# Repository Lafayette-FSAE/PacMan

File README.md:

# PacMan
A KiCad Schematic for PacMan, a Accumulator Management Board for the Lafayette FSAE Accumulator Management System

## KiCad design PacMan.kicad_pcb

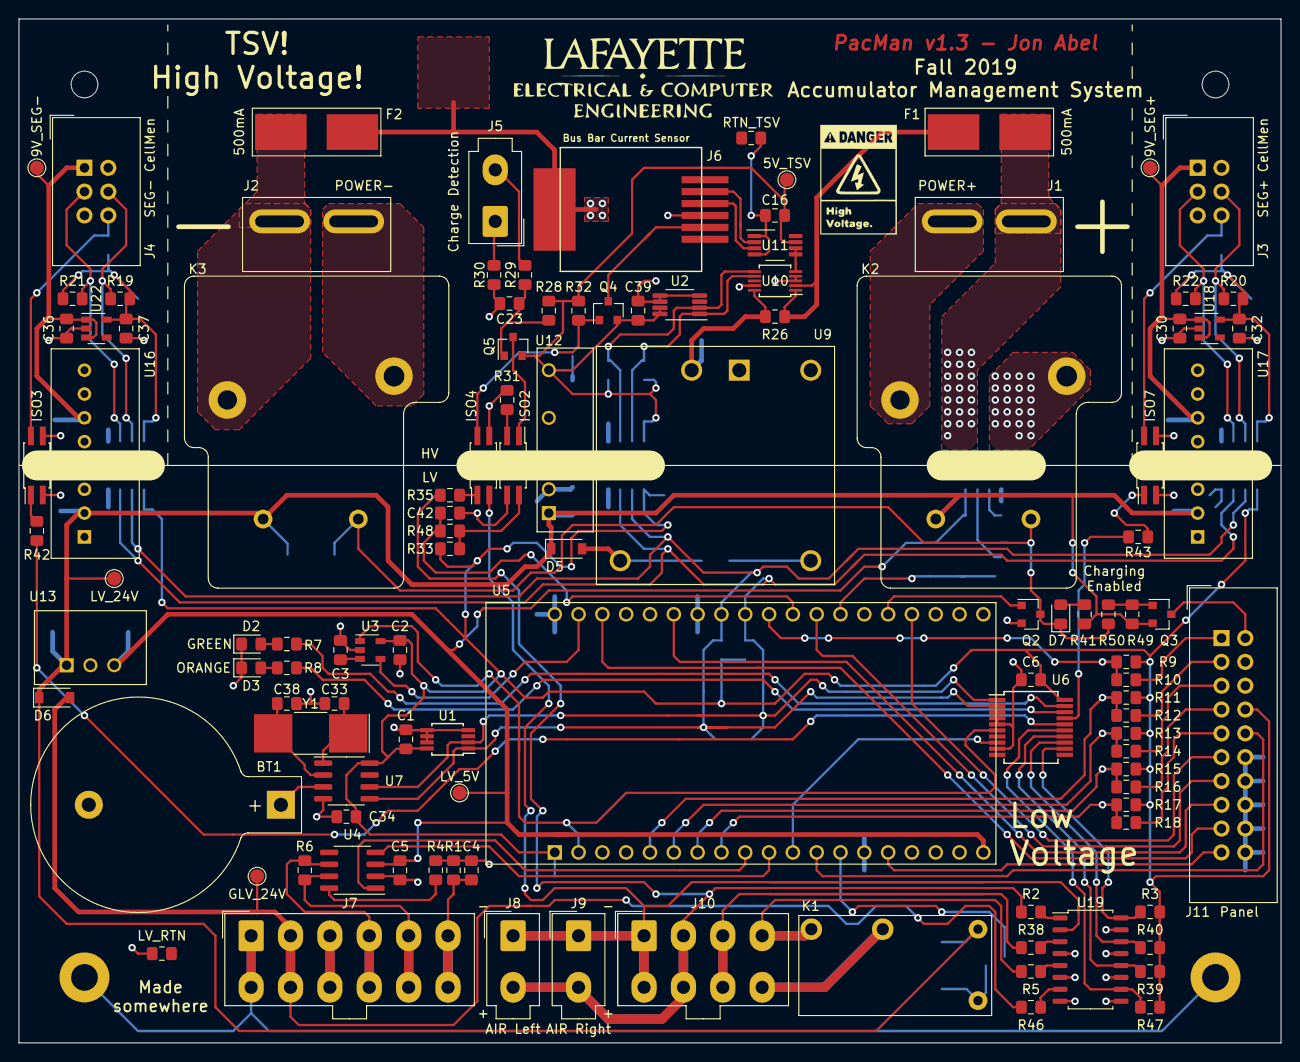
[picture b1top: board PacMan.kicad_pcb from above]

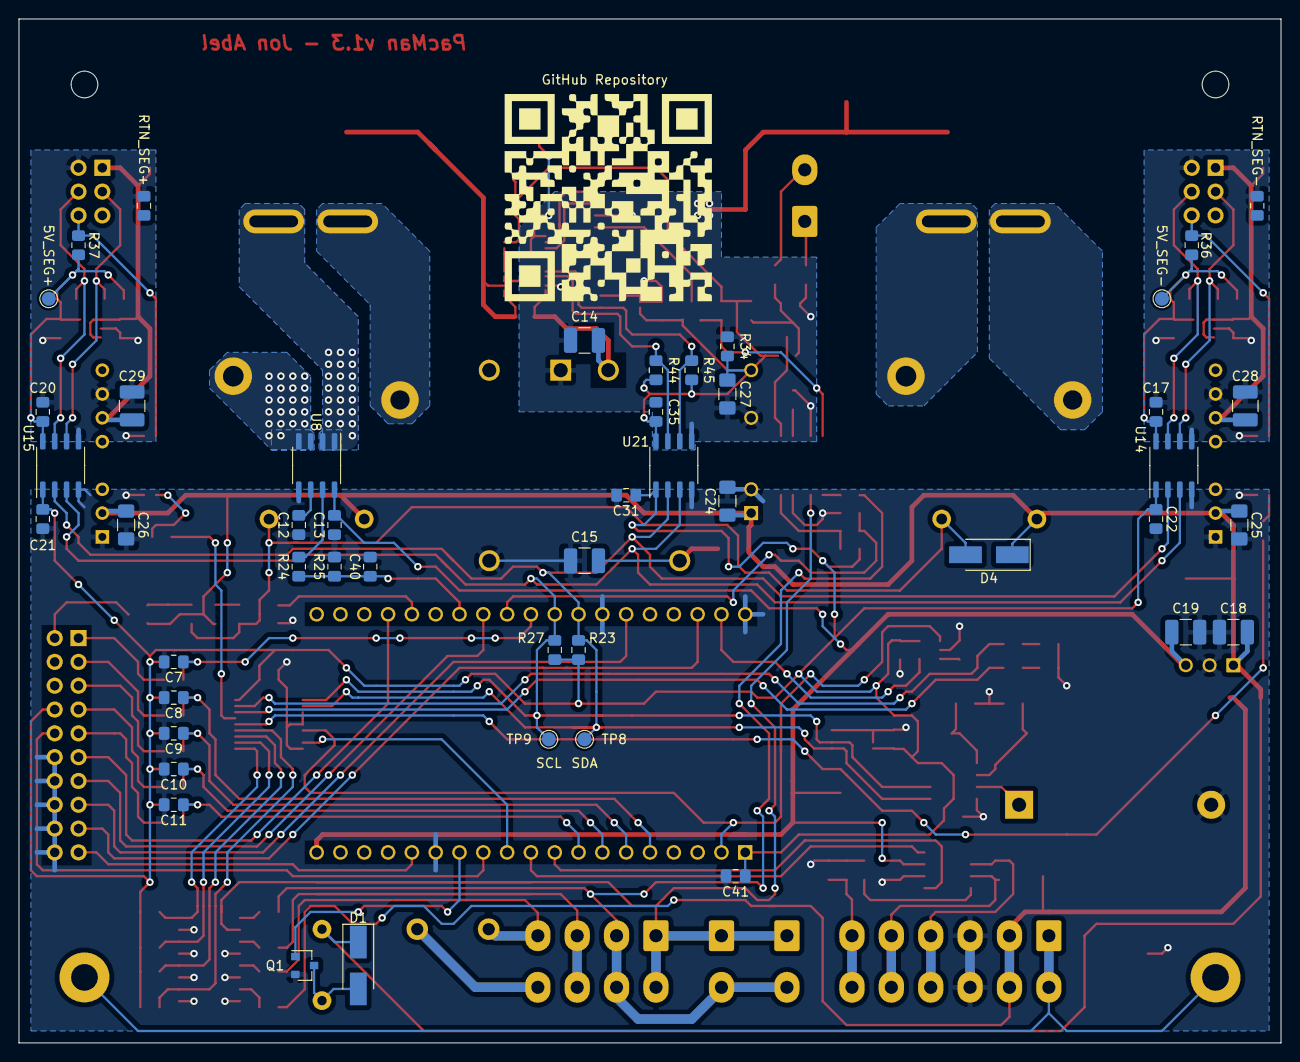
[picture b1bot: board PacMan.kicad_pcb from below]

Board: 2 copper layers, 134.6 x 109.2 mm, 168 parts (47 on the bottom side), 105 nets.

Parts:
BT1: BR1225; BatteryHolder_Keystone_103_1x20mm
C1, C2, C3, C5, C6, C7, C8, C9, C10, C11, C16, C17, C20, C21, C22, C23, C31, C35, C39: 0.1u/50V; C_0805_2012Metric_Pad1.15x1.40mm_HandSolder
C4, C42: C; C_0805_2012Metric_Pad1.15x1.40mm_HandSolder
C12: 1n/50V; C_0805_2012Metric_Pad1.15x1.40mm_HandSolder
C13, C30, C34, C36, C40, C41: 1u/50V; C_0805_2012Metric_Pad1.15x1.40mm_HandSolder
C14: 4.7u/100V; C_1210_3225Metric_Pad1.42x2.65mm_HandSolder
C15, C18, C28, C29: 10u/50V; C_1210_3225Metric_Pad1.42x2.65mm_HandSolder
C19: 22u/25V; C_1210_3225Metric_Pad1.42x2.65mm_HandSolder
C24, C25, C26, C27: 4.7uF/50V; C_1206_3216Metric_Pad1.42x1.75mm_HandSolder
C32, C37: 2.2u/25V; C_0805_2012Metric_Pad1.15x1.40mm_HandSolder
C33, C38: 20p; C_0805_2012Metric_Pad1.15x1.40mm_HandSolder
D1, D4: S1B; D_SMA_Handsoldering
D2: LED_GREEN; LED_0805_2012Metric_Pad1.15x1.40mm_HandSolder
D3: LED_ORANGE; LED_0805_2012Metric_Pad1.15x1.40mm_HandSolder
D5, D6: 1N5819HW; D_SOD-123
D7: LED_CHRG; LED_0805_2012Metric_Pad1.15x1.40mm_HandSolder
F1, F2: 500mA; 0154.500DRL
H1, H2: MountingHole_NoPad_#4; MountingHole_#4_NoPad
H3, H4: MountingHole_Pad_#4; MountingHole_#4_Pad
ISO2, ISO3, ISO4, ISO7: TLP293; SO-4_4.4x2.3mm_P1.27mm
J1: POWER+; Powerpole_PP45_FP_1x2
J2: POWER-; Powerpole_PP45_FP_1x2
J3: SEG+ CellMen; IDC-Header_2x03_P2.54mm_Vertical
J4: SEG- CellMen; IDC-Header_2x03_P2.54mm_Vertical
J5: Charge Detection; Molex_Mini-Fit_Jr_5566-02A_2x01_P4.20mm_Vertical
J6: BusBar Current Sensor; MOLEX_RJ11
J7: GLV/CAN; Molex_Mini-Fit_Jr_5566-12A_2x06_P4.20mm_Vertical
J8: AIR Left; Molex_Mini-Fit_Jr_5566-02A_2x01_P4.20mm_Vertical
J9: AIR Right; Molex_Mini-Fit_Jr_5566-02A_2x01_P4.20mm_Vertical
J10: SLOOP; Molex_Mini-Fit_Jr_5566-08A_2x04_P4.20mm_Vertical
J11: Panel; Amphenol_IDC-Header_2x10_P2.54mm_Vertical
K1: G5Q-1A4 DC24; G5Q-1A4
K2, K3: T9AS1D12-24; T9AS1D12
LOGO1: LafECEDepLogo; ECE_Logo_Jon
LOGO2: LeopardPawLogo; paw_solder_mask_bigly
LOGO3: DangerHighVoltageLogo; highvoltagesmall
Q1, Q2: DMN3730U; SOT-23
Q3, Q4, Q5: DMP10H4D2S; SOT-23
R1: 1M; R_0805_2012Metric_Pad1.15x1.40mm_HandSolder
R2, R5, R35, R38, R46: 5.1k; R_0805_2012Metric_Pad1.15x1.40mm_HandSolder
R3, R24, R32, R33, R36, R37, R39, R40, R47: 10k; R_0805_2012Metric_Pad1.15x1.40mm_HandSolder
R4, R10, R12, R14, R16, R18, R41: 1k; R_0805_2012Metric_Pad1.15x1.40mm_HandSolder
R6: 120; R_0805_2012Metric_Pad1.15x1.40mm_HandSolder
R7, R8, R42, R43: 270; R_0805_2012Metric_Pad1.15x1.40mm_HandSolder
R9, R11, R13, R15, R17, R28: 100k; R_0805_2012Metric_Pad1.15x1.40mm_HandSolder
R19, R20, R21, R22, R23, R27, R44, R45: 3.3k; R_0805_2012Metric_Pad1.15x1.40mm_HandSolder
R25: 22k; R_0805_2012Metric_Pad1.15x1.40mm_HandSolder
R26: 0.82; R_0805_2012Metric_Pad1.15x1.40mm_HandSolder
R29, R30: 5k; R_0805_2012Metric_Pad1.15x1.40mm_HandSolder
R31: 330; R_0805_2012Metric_Pad1.15x1.40mm_HandSolder
R34: 470; R_0805_2012Metric_Pad1.15x1.40mm_HandSolder
R48: R; R_0805_2012Metric_Pad1.15x1.40mm_HandSolder
R49, R50: 4.7k; R_0805_2012Metric_Pad1.15x1.40mm_HandSolder
TP1: 5V_SEG-; TestPoint_Pad_D1.5mm
TP2: RTN_SEG-; R_0805_2012Metric_Pad1.15x1.40mm_HandSolder
TP3: 9V_SEG-; TestPoint_Pad_D1.5mm
TP4: LV_RTN; R_0805_2012Metric_Pad1.15x1.40mm_HandSolder
TP5: LV_5V; TestPoint_Pad_D1.5mm
TP6: LV_24V; TestPoint_Pad_D1.5mm
TP7: GLV_24V; TestPoint_Pad_D1.5mm
TP8: SDA; TestPoint_Pad_D1.5mm
TP9: SCL; TestPoint_Pad_D1.5mm
TP10: 5V_TSV; TestPoint_Pad_D1.5mm
TP11: RTN_TSV; R_0805_2012Metric_Pad1.15x1.40mm_HandSolder
TP12: 9V_SEG+; TestPoint_Pad_D1.5mm
TP13: 5V_SEG+; TestPoint_Pad_D1.5mm
TP14: RTN_SEG+; R_0805_2012Metric_Pad1.15x1.40mm_HandSolder
U1, U2: MCP9804; MSOP-8_3x3mm_P0.65mm
U3: ADM6320; SOT-23-5
U4: MCP2551-I-SN; SOIC-8_3.9x4.9mm_P1.27mm
U5: ESP32_DEVKITC; MODULE_ESP32-DEVKITC-32D
U6: MCP23008; SSOP-20_5.3x7.2mm_P0.65mm
U7: BQ32002; SOIC-8_3.9x4.9mm_P1.27mm
U8: ACHS-7122; SO-8_3.9x4.9mm_P1.27mm
U9: PDQE10-Q48-S24-D; PDQE10-DIP6
U10: LTC4151; MSOP-10_3x3mm_P0.5mm
U11: INA592; VSSOP-8_3.0x3.0mm_P0.65mm
U12: MEF1S2405SP3C
U13: V7805-500; VX7805-500
U14, U15, U21: Si8600AC; SO-8_3.9x4.9mm_P1.27mm
U16, U17: TEC3-2419
U18, U22: AP2204K-5.0; SOT-23-5
U19: TLP293-4; SOIC-16_4.55x10.3mm_P1.27mm
Y1: 32K; Crystal_SMD_SeikoEpson_MC405-2Pin_9.6x4.1mm

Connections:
/5V_SEG+: C20.1, C32.1, R20.1, R22.1, R37.1, TP13.1, U15.8, U18.5
/5V_SEG-: C17.1, C37.1, R19.1, R21.1, R36.1, TP1.1, U14.8, U22.5
/5V_TSV: C16.2, C27.1, C35.1, C39.1, Q4.2, Q5.2, R28.1, R32.1, R34.1, R44.1, R45.1, TP10.1, U2.7, U2.8, U11.7, U12.7, U21.8
/9V_SEG+: C29.1, C30.1, J3.1, TP12.1, U17.6, U18.1, U18.3
/9V_SEG-: C28.1, C36.1, J4.1, TP3.1, U16.6, U22.1, U22.3
/AIRS+: J8.2, J9.2, J10.2, J10.6, R2.2, R35.2
/AIRS-: ISO4.2, J8.1, J9.1, J10.1, J10.5, U19.2
/AMPS_PWR: J6.5, Q4.3
/BTN_CENTER: J11.9, R18.1
/BTN_DOWN: J11.7, R16.1
/BTN_LEFT: J11.1, R10.1
/BTN_RIGHT: J11.3, R12.1
/BTN_UP: J11.5, R14.1
/CAN_H: J7.5, J7.11, R6.1, U4.7
/CAN_L: J7.4, J7.10, R6.2, U4.6
/CAN_SHIELD: C4.2, J7.6, J7.12, R1.2
/CHRG_CURRENT: C40.1, R24.1, R25.1, U5.32
/CHRG_DETECT+: J5.2, R29.2
/CHRG_DETECT-: J5.1, R30.2
/CHRG_EN: Q2.1, U5.34
/CHRG_IN+: J1.2, K2.3
/CHRG_IN-: J2.1, K3.4
/CHRG_LED: J11.2, Q3.3
/CHS_GND: H3.1, H4.1, J7.1, J7.7
/Charging/CurrentSensor+: K2.4, U8.3, U8.4
/DCHRG_A1: J6.3, U11.3
/DCHRG_A2: J6.2, U11.2
/DISP_BUSY: J11.13, U5.31
/DISP_CLK: J11.10, U5.12
/DISP_CS: J11.11, U5.35
/DISP_DC: J11.17, U5.22
/DISP_DIN: J11.19, U5.15
/DISP_RST: J11.15, U5.25
/GLV_24V: D6.2, J7.2, J7.8, R46.2, TP7.1
/GLV_RTN: BT1.2, C1.2, C2.2, C3.2, C4.1, C5.2, C6.2, C7.2, C8.2, C9.2, C10.2, C11.2, C12.2, C13.2, C15.2, C18.2, C19.2, C21.2, C22.2, C24.2, C25.2, C26.2, C31.2, C33.2, C34.2, C38.2, C40.2, C41.2, C42.2, D2.1, D3.1, ISO2.3, ISO3.2, ISO7.2, J7.3, J7.9, J11.12, J11.14, J11.16, J11.18, J11.20, Q1.2, Q2.2, R1.1, R4.1, R25.2, TP4.1, U1.4, U1.5, U1.6, U1.7, U3.2, U4.2, U5.14, U5.20, U5.26, U6.3, U6.4, U6.5, U6.9, U7.4, U8.5, U9.5, U12.2, U13.2, U14.4, U15.4, U16.1, U17.1, U19.4, U19.6, U19.8, U19.9, U19.11, U19.13, U19.15, U21.4
/Isolation/EN_AMPS: ISO4.4, Q4.1, R32.2
/LV_3V3: C1.1, C2.1, C6.1, C21.1, C22.1, C31.1, C34.1, C41.1, J11.8, R3.2, R9.1, R11.1, R13.1, R15.1, R17.1, R23.1, R27.1, R33.2, R39.2, R40.2, R47.2, U1.8, U3.5, U5.1, U6.20, U7.8, U14.1, U15.1, U21.1
/LV_5V: C5.1, C13.1, C19.1, TP5.1, U4.3, U5.19, U8.8, U13.3
/LV_24V: C18.1, C24.1, C25.1, C26.1, D1.1, D4.1, D5.1, D6.1, K1.1, K2.1, K3.1, Q3.2, R41.1, R49.1, TP6.1, U12.1, U13.1, U16.2, U17.2
/MCU/AIRS_STATUS: R3.1, U6.12, U19.16
/MCU/BTN_CENTER_MCU: C11.1, R17.2, R18.2, U5.8
/MCU/BTN_DOWN_MCU: C10.1, R15.2, R16.2, U5.7
/MCU/BTN_LEFT_MCU: C7.1, R9.2, R10.2, U5.29
/MCU/BTN_RIGHT_MCU: C8.1, R11.2, R12.2, U5.5
/MCU/BTN_UP_MCU: C9.1, R13.2, R14.2, U5.6
/MCU/CANRX: U4.4, U5.10
/MCU/CANTX: U4.1, U5.9
/MCU/GLV_STATUS: R47.1, U6.15, U19.10
/MCU/IO_INT: U5.11, U6.8
/MCU/LED_G: R7.1, U6.19
/MCU/LED_O: R8.1, U6.18
/MCU/SLOOP1_STATUS: R39.1, U6.14, U19.12
/MCU/SLOOP2_STATUS: R40.1, U6.13, U19.14
/MCU/SLOOP_EN: Q1.1, U5.13
/MCU/WATCHDOG: U3.4, U5.21
/MCU/~RESET: U3.1, U5.2, U6.6
/PACK+: F1.1, J1.1, U8.1, U8.2
/PACK-: F2.1, J2.2, K3.3
/PACK_FUSED: F1.2, R26.2, U10.1, U10.2
/PACK_RTN: C14.2, C16.1, C23.2, C27.2, C35.2, C39.2, F2.2, ISO4.3, J6.4, J6.SH, R30.1, R31.1, R34.2, TP11.1, U2.4, U2.5, U2.6, U9.1, U10.3, U10.4, U10.9, U11.1, U11.4, U12.5, U21.5
/Power/DCHRG_CURRENT: U10.5, U11.5, U11.6
/Power/PACK_FUSED_CS: C14.1, R26.1, U9.2, U10.10
/RST_GLV_SEG+: R43.2, U6.17
/RST_GLV_SEG-: R42.2, U6.16
/RST_SEG+: ISO7.4, J3.6, R37.2
/RST_SEG-: ISO3.4, J4.6, R36.2
/RTN_SEG+: C20.2, C29.2, C30.2, C32.2, ISO7.3, J3.2, TP14.1, U15.5, U17.7, U18.2
/RTN_SEG-: C17.2, C28.2, C36.2, C37.2, ISO3.3, J4.2, TP2.1, U14.5, U16.7, U22.2
/SCL_GLV: R27.2, TP9.1, U1.2, U5.28, U6.1, U7.6, U14.3, U15.3, U21.3
/SCL_SEG+: J3.3, R22.2, U15.6
/SCL_SEG-: J4.3, R21.2, U14.6
/SCL_TSV: R45.2, U2.2, U10.6, U21.6
/SDA_GLV: R23.2, TP8.1, U1.1, U5.27, U6.2, U7.5, U14.2, U15.2, U21.2
/SDA_SEG+: J3.4, R20.2, U15.7
/SDA_SEG-: J4.4, R19.2, U14.7
/SDA_TSV: R44.2, U2.1, U10.7, U21.7
/SLOOP1_IN: J10.4, K1.4, R5.2
/SLOOP1_OUT: J10.8, K1.3
/SLOOP2: J10.3, J10.7, R38.2
/~CHRG_DETECT: C42.1, R48.1, U5.30
unnamed: BT1.1, U7.3
unnamed: C3.1, U3.3
unnamed: C12.1, U8.6
unnamed: C15.1, D5.2, U9.3
unnamed: C23.1, Q5.1, R28.2, R29.1
unnamed: C33.1, U7.1, Y1.1
unnamed: C38.1, U7.2, Y1.2
unnamed: D1.2, K1.2, Q1.3
unnamed: D2.2, R7.2
unnamed: D3.2, R8.2
unnamed: D4.2, D7.1, K2.2, K3.2, Q2.3, R50.2
unnamed: D7.2, R41.2
unnamed: ISO2.1, Q5.3
unnamed: ISO2.2, R31.2
unnamed: ISO2.4, R33.1, R48.2
unnamed: ISO3.1, R42.1
unnamed: ISO4.1, R35.1
unnamed: ISO7.1, R43.1
unnamed: Q3.1, R49.2, R50.1
unnamed: R2.1, U19.1
unnamed: R4.2, U4.8
unnamed: R5.1, U19.5
unnamed: R24.2, U8.7
unnamed: R38.1, U19.3
unnamed: R46.1, U19.7

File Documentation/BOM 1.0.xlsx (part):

C4 | C | Capacitor_SMD:C_0805_2012Metric_Pad1.15x1.40mm_HandSolder | ~ |  |  |  |  | 1
> C1-C3, C5-C11, C16, C22-C25 | 0.1u/50V | Capacitor_SMD:C_0805_2012Metric_Pad1.15x1.40mm_HandSolder | http://www.samsungsem.com/kr/support/product-search/mlcc/__i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 | Samsung Electro-Mechanics | CL21B104KBCNNNC | Digikey | 1276-1003-1-ND | 15
C12 | 1n/50V | Capacitor_SMD:C_0805_2012Metric_Pad1.15x1.40mm_HandSolder | http://www.samsungsem.com/kr/support/product-search/mlcc/__i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 | Samsung Electro-Mechanics | CL21B102KBCNNNC | Digikey | 1276-2425-1-ND | 1
C13 | 1u/50V | Capacitor_SMD:C_0805_2012Metric_Pad1.15x1.40mm_HandSolder | http://www.samsungsem.com/kr/support/product-search/mlcc/__i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 | Samsung Electro-Mechanics | CL21B105KBFNNNG | Digikey | 1276-6470-1-ND | 1
C14 | 4.7u/100V | Capacitor_SMD:C_0805_2012Metric_Pad1.15x1.40mm_HandSolder | http://www.samsungsem.com/kr/support/library/product-catalog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 | Samsung Electro-Mechanics | CL32B475KCVZW6E | Digikey | 1276-7060-1-ND | 1
> C15, C18, C20 | 10u/50V | Capacitor_SMD:C_1210_3225Metric_Pad1.42x2.65mm_HandSolder | http://www.samsungsem.com/kr/support/product-search/mlcc/__i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 | Samsung Electro-Mechanics | CL32B106KBJNNWE | Digikey | 1276-3388-1-ND | 3
C17 | 22u/50V | Capacitor_SMD:C_0805_2012Metric_Pad1.15x1.40mm_HandSolder | http://www.samsungsem.com/kr/support/product-search/mlcc/__i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 | Samsung Electro-Mechanics | CL21A475KBQNNNE | Digikey | 1276-1248-1-ND | 1
C19 | 22u/25V | Capacitor_SMD:C_1210_3225Metric_Pad1.42x2.65mm_HandSolder | http://www.samsungsem.com/kr/support/product-search/mlcc/__i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 | Samsung Electro-Mechanics | CL32B226KAJNFNE | Digikey | 1276-3391-1-ND | 1
C21 | 0.33u/50V | Capacitor_SMD:C_0805_2012Metric_Pad1.15x1.40mm_HandSolder | http://www.samsungsem.com/kr/support/product-search/mlcc/__i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 | Samsung Electro-Mechanics | CL21B334KBFNNNE | Digikey | 1276-1123-1-ND | 1
> D1, D4 | S1B | Diode_SMD:D_SMA_Handsoldering | https://www.diodes.com/assets/Datasheets/ds16003.pdf | Diodes Incorporated | S1B-13-F | Digikey | S1B-FDICT-ND | 2
D2 | LED_GREEN | LED_SMD:LED_0805_2012Metric_Pad1.15x1.40mm_HandSolder | https://media.digikey.com/pdf/Data%20Sheets/Lite-On%20PDFs/L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 | Lite-On Inc. | LTST-C170GKT | Digikey | 160-1179-1-ND | 1
D3 | LED_ORANGE | LED_SMD:LED_0805_2012Metric_Pad1.15x1.40mm_HandSolder | http://optoelectronics.liteon.com/upload/download/DS-22-99-0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 | Lite-On Inc. | LTST-C171AKT | Digikey | 160-1419-1-ND | 1
> D5, D6 | 1N5819HW | Diode_SMD:D_SOD-123 | https://www.diodes.com/assets/Datasheets/ds30217.pdf | Diodes Incorporated | 1N5819HW-7-F | Digikey | 1N5819HW-FDICT-ND | 2
F1 | Pack+ | Lafayette_Electric_Car_Footprints:0154.500DRL | https://www.littelfuse.com/~/media/electronics/datasheets/fu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 | Littelfuse Inc. | 0154.500DRL | Digikey | F6776CT-ND | 1
F2 | Pack- | Lafayette_Electric_Car_Footprints:0154.500DRL | https://www.littelfuse.com/~/media/electronics/datasheets/fu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 | Littelfuse Inc. | 0154.500DRL | Digikey | F6776CT-ND | 1
> H1-H4 | MountingHole_Pad | MountingHole:MountingHole_4.3mm_M4_Pad | ~ |  |  |  |  | 4
> ISO1-ISO4 | TLP293 | Package_SO:SO-4_4.4x2.3mm_P1.27mm | https://toshiba.semicon-storage.com/info/docget.jsp?did=1441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 | Toshiba Semiconductor | TLP293(GR-TPL,E | Digikey | TLP293(GR-TPLECT-ND | 4
J1 | POWER+ | Lafayette_Electric_Car_Footprints:DF22-2P-7.92 | https://www.hirose.com/product/document?clcode=CL0680-1074-0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 | Hirose Electric Co | DF22L-2P-7.92DSA(05) | Digikey | H10722-ND | 1
J2 | POWER- | Lafayette_Electric_Car_Footprints:DF22-2P-7.92 | https://www.hirose.com/product/document?clcode=CL0680-1074-0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 | Hirose Electric Co | DF22R-2P-7.92DSA(05) | Digikey | H10718-ND | 1
J3 | TSV IN | Lafayette_Electric_Car_Footprints:Molex_Mini-Fit_Jr_5566-02A_2x01_P4.20mm_Verti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 | https://www.molex.com/webdocs/datasheets/pdf/en-us/172447020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 | Molex | 1724470202 | Digikey | WM17931-ND | 1
J4 | Charge Detection | Lafayette_Electric_Car_Footprints:Molex_Mini-Fit_Jr_5566-02A_2x01_P4.20mm_Verti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 | https://www.molex.com/webdocs/datasheets/pdf/en-us/172447020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 | Molex | 1724470202 | Digikey | WM17931-ND | 1
J5 | CellMen | Connector_IDC:IDC-Header_2x03_P2.54mm_Vertical | https://cdn.amphenol-icc.com/media/wysiwyg/files/drawing/75869.pdf | Amphenol ICC | 75869-131LF | Digikey | 609-2845-ND | 1
J6 | RJ12 | Lafayette_Electric_Car_Footprints:MOLEX_RJ11 | https://www.molex.com/pdm_docs/sd/855135002_sd.pdf | Molex | 855135002 | Digikey | WM3789CT-ND | 1
J7 | Panel | Lafayette_Electric_Car_Footprints:Amphenol_IDC-Header_2x10_P2.54mm_Vertical | https://cdn.amphenol-icc.com/media/wysiwyg/files/drawing/75869.pdf | Amphenol ICC | 75869-304LF | Digikey | 609-5118-ND | 1
J8 | SLOOP | Lafayette_Electric_Car_Footprints:Molex_Mini-Fit_Jr_5566-08A2_2x04_P4.20mm_Vert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 | https://www.molex.com/pdm_docs/sd/1724470002_sd.pdf | Molex | 1724470008 | Digikey | WM20746-ND | 1
J9 | GLV/CAN | Lafayette_Electric_Car_Footprints:Molex_Mini-Fit_Jr_5566-12A2_2x06_P4.20mm_Vert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 | https://www.molex.com/pdm_docs/sd/462070012_sd.pdf | Molex | 462070012 | Digikey | 23-0462070012-ND | 1
J12 | CHRG TEST | Connector_PinHeader_2.54mm:PinHeader_1x02_P2.54mm_Vertical | ~ |  |  |  |  | 1
J13 | AIR Left | Lafayette_Electric_Car_Footprints:Molex_Mini-Fit_Jr_5566-02A_2x01_P4.20mm_Verti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 | https://www.molex.com/webdocs/datasheets/pdf/en-us/172447020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 | Molex | 1724470202 | Digikey | WM17931-ND | 1
J14 | AIR Right | Lafayette_Electric_Car_Footprints:Molex_Mini-Fit_Jr_5566-02A_2x01_P4.20mm_Verti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 | https://www.molex.com/webdocs/datasheets/pdf/en-us/172447020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 | Molex | 1724470202 | Digikey | WM17931-ND | 1
K1 | G5Q-1A4 DC24 | Lafayette_Electric_Car_Footprints:G5Q-1A4 | https://omronfs.omron.com/en_US/ecb/products/pdf/en-g5q.pdf | Omron Electronics | G5Q-1A4 DC24 | Digikey | Z224-ND | 1
> K2, K3 | T9AS1D12-48 | Lafayette_Electric_Car_Footprints:T9AS1D12 | https://www.te.com/commerce/DocumentDelivery/DDEController?A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 | TE Connectivity | T9AS1D12-48 | Digikey | PB1013-ND | 2
LOGO1 | LafECEDepLogo | Lafayette_Electric_Car_Footprints:ECE_Logo_Jon |  |  |  |  |  | 1
LOGO2 | LeopardPawLogo | Lafayette_Electric_Car_Footprints:paw_solder_mask_larger |  |  |  |  |  | 1
LOGO3 | DangerHighVoltageLogo | Lafayette_Electric_Car_Footprints:highvoltagesmall |  |  |  |  |  | 1
> Q1, Q3 | BSS123 | Package_TO_SOT_SMD:SOT-23_Handsoldering | https://www.diodes.com/assets/Datasheets/ds30366.pdf | Diodes Incorporated | BSS123-7-F | Digikey | BSS123-FDICT-ND | 2
> Q2, Q4 | DMP10H4D2S | Package_TO_SOT_SMD:SOT-23_Handsoldering | https://www.diodes.com/assets/Datasheets/DMP10H4D2S.pdf | Diodes Incorporated | DMP10H4D2S-7 | Digikey | DMP10H4D2S-7DICT-ND | 2
R1 | 1M | Resistor_SMD:R_0805_2012Metric_Pad1.15x1.40mm_HandSolder | ~ |  |  |  |  | 1
> R2, R28, R33-R37 | 4.7k | Resistor_SMD:R_0805_2012Metric_Pad1.15x1.40mm_HandSolder | ~ |  |  |  |  | 7
> R3, R24, R32 | 10k | Resistor_SMD:R_0805_2012Metric_Pad1.15x1.40mm_HandSolder | ~ |  |  |  |  | 3
> R4, R10, R12, R14, R16, R18, R22 | 1k | Resistor_SMD:R_0805_2012Metric_Pad1.15x1.40mm_HandSolder | ~ |  |  |  |  | 7
R6 | 120 | Resistor_SMD:R_0805_2012Metric_Pad1.15x1.40mm_HandSolder | ~ |  |  |  |  | 1
> R7, R8 | 270 | Resistor_SMD:R_0805_2012Metric_Pad1.15x1.40mm_HandSolder | ~ |  |  |  |  | 2
> R9, R11, R13, R15, R17 | 100k | Resistor_SMD:R_0805_2012Metric_Pad1.15x1.40mm_HandSolder | ~ |  |  |  |  | 5
R19 | 15k | Resistor_SMD:R_0805_2012Metric_Pad1.15x1.40mm_HandSolder | ~ |  |  |  |  | 1
> R20, R21 | 560 | Resistor_SMD:R_0805_2012Metric_Pad1.15x1.40mm_HandSolder | ~ |  |  |  |  | 2
R23 | 390 | Resistor_SMD:R_0805_2012Metric_Pad1.15x1.40mm_HandSolder | ~ |  |  |  |  | 1
R25 | 22k | Resistor_SMD:R_0805_2012Metric_Pad1.15x1.40mm_HandSolder | ~ |  |  |  |  | 1
R26 | 0.82 | Resistor_SMD:R_0805_2012Metric_Pad1.15x1.40mm_HandSolder | https://industrial.panasonic.com/cdbs/www-data/pdf/RDN0000/A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 | Panasonic Electronic Components | ERJ-6DQFR82V | Digikey | P19306CT-ND | 1
R27 | R | Resistor_SMD:R_0805_2012Metric_Pad1.15x1.40mm_HandSolder | ~ |  |  |  |  | 1
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
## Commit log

2019-10-08 Created blank schematic
2019-11-08 lotsa work
2019-11-08 more files
2019-11-10 v0.1, basic components on schematic
2019-11-11 Additional components and connectors, resistor sizing, etc.
2019-11-11 New power monitor, panel outputs and filtering, shunt resistor
2019-11-12 Routed almost everything, general design mostly complete
2019-11-13 Spec'd some parts
2019-11-13 Weird cache stuff
2019-11-13 More part speccing
2019-11-13 updated footprints
2019-11-14 Started work on board layout
2019-11-15 go on, look, see if I care
2019-11-15 routing
2019-11-18 added like 2 traces
2019-11-18 Changed/added some footprints for AIR and ChrgDetect connectors
2019-11-18 Routing + 3D models
2019-11-18 guess
2019-11-18 5ish more traces left wawaweewa
2019-11-19 filled out some parts information
2019-11-19 0 unrouted babyyyyyyyyy
2019-11-19 Gerber files from first review/quote
2019-11-19 GTD file
2019-11-19 Ordered board, GTD file, panelized gerbers
2019-11-19 v1.0
2019-11-20 Created schematic pdf for 1.0
2019-11-22 Added things to fix text file
2019-12-04 Updated Things to fix and added a render file
2019-12-07 Added BOM, some PDFs, updated schematic version to 1.1 for updates
2019-12-09 Updated things to fix, output some new renders, updated schematic to 1.1 to start changing
2020-01-04 Switched some pins around, added SLOOP isolators to measure SLOOP1in and SLOOP2
2020-01-04 brought in the updated fuse footprint and cleaned up some tracks
2020-01-04 removed fp-info-cache from git tracking
2020-01-06 made the board smaller
2020-01-07 starting the rework to fix the AMS isolation error
2020-01-07 Updated date for version on PCB
2020-01-08 Switched the control loops for the charging relays to GLV
2020-01-10 Updated some power stuff
2020-01-11 Started work on new layout
2020-01-11 quick change
2020-01-12 Added connectors for cell balancing, made big progress on new layout
2020-01-13 Just about finished the layout
2020-01-13 Started adding active charge measurement
2020-01-14 Added RTC onto board
2020-01-14 Schematic work, placed some components on the PCB
2020-01-14 started moving over to new esp dev kit
2020-01-15 Re-layout to account for the new esp32, put on the RTC, the balancing measurement stuff, pretty much finished up the board, added some comments to schematic and other changes
2020-01-15 switched some ESP32 pins around, hopefully fixed some grounding stuff, cleaned up schematic naming slightly
2020-01-17 Added connection to IO expander interrupt pin
2020-01-17 Added some planes around the balancing connectors and added the QRCode to the github page
2020-01-19 started re-routing for adjusted symmetric design
2020-01-20 incremental work
2020-01-20 Fixed a little bit of stuff
2020-01-21 completed reroute
2020-01-21 updayed relayfootprint and fixed chassis trace
2020-01-21 Cleaned up some spacing, silkscreen, qrcode
2020-01-21 Added CellMen reset lines and routed them
2020-01-22 quick track fix
2020-01-22 Output some gerber files and pushed some title block info
2020-01-22 Added panelized production files
2020-01-22 changed date, added i2c address
2020-01-24 made some holes NPTH, exported some new gerbers
2020-01-30 added some dimensions and fixed the silkscreen slot
2020-02-04 added emergency gerber files, yay
2020-02-04 switched to new holes instead of slots, more gerbers
2020-02-04 jk here's the change
2020-02-11 updated resistor values
2020-02-13 Fixed the upside down PMOS transistors
2020-02-20 Updated schematic with new names for SEG1 and SEG2, added temp sensor, added the 5V converter 3D model
2020-02-21 Updated PCB design to match schematic changes, played with spacings
2020-02-24 added GLV measurement point, switched to a 16 pin 4 in 1 isolator
2020-02-26 added filter cap to ADC measurement channel
2020-03-05 Fixed the issue with the ADC pins (VP and VN), did some rerouting, slight silkscreen changes
2020-03-05 quick little routing thing
2020-03-05 a bit of dimensioning
2020-03-12 Maybe final version of PacMan
2020-03-30 Removed some old files
2020-04-09 Added comments to the schematic, changed some formatting, made the charge LED a high side switch, some small value changes, layout update
2020-04-09 added BOM and render file
2020-04-14 Added 3D models for connectors, relabeled some connectors
2020-04-14 added some mates with fields for the connectors
2020-04-16 added pinout file
